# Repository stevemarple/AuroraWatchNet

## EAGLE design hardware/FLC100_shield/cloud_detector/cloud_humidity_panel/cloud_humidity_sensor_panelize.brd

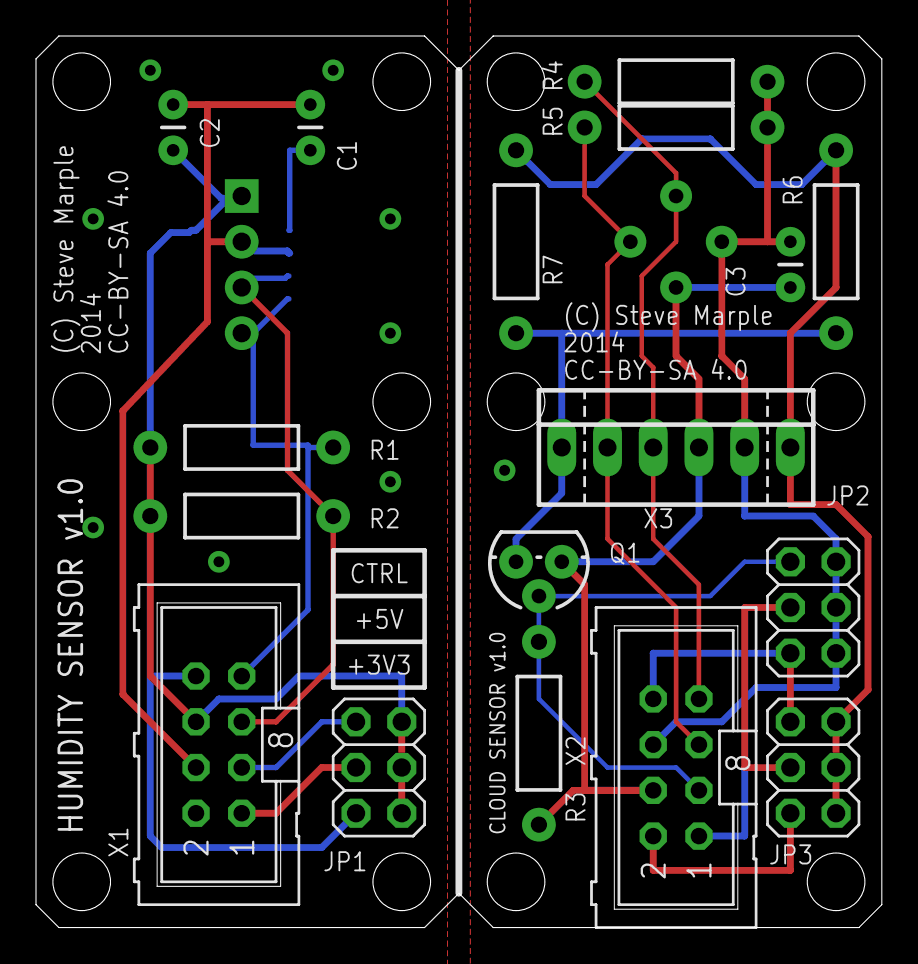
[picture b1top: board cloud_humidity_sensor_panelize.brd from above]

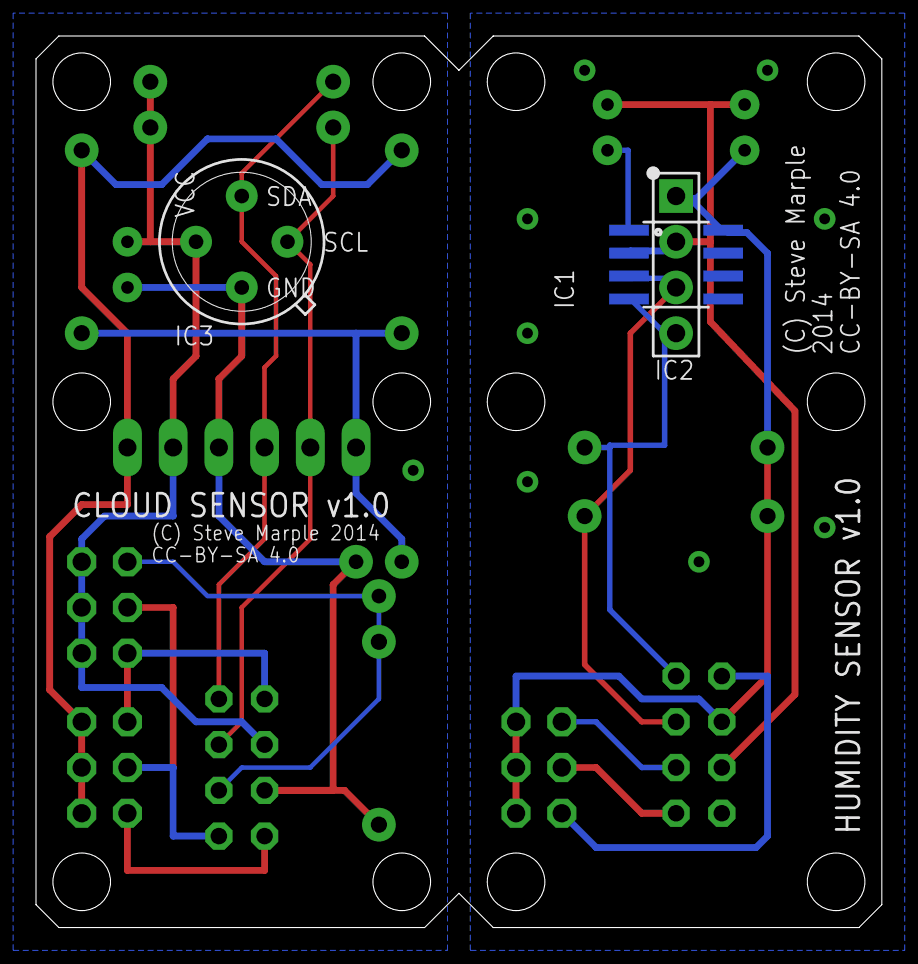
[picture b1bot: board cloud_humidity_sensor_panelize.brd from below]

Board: 2 copper layers, 47.0 x 49.5 mm, 20 parts (3 on the bottom side), 18 nets.

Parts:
C1, C3: 100n; CAP-PTH-SMALL
C2: 220n; CAP-PTH-SMALL
IC1: HIH613x; SO08
IC2: HIH612x; SIL04
IC3: MLX90614; TO39-4
JP1, JP2: VCC; 2X03
JP3: HEAT VCC; 2X03
Q1: 2N7000; TO-92
R1, R2, R4, R5: 10k; RES-AXIAL-0.4
R3: 1M; RES-AXIAL-0.4
R6, R7: 100R; RES-AXIAL-0.4
X1: FLC100 SHIELD; ML8
X2: SHIELD; ML8
X3: SENSOR; 22-23-2061

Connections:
+3V1: JP2.2, JP3.1, X2.8
+3V3: JP1.2, X1.8
+5V: JP1.4, X1.1
+5V1: JP2.4, JP3.3, X2.1
CONTROL: JP1.6, X1.3
CONTROL1: JP2.6, Q1.2, R3.P$2, X2.3
GND: C1.2, C2.2, IC1.2, IC2.2, X1.4
GND1: C3.2, IC3.4, Q1.1, R3.P$1, X2.4, X3.4
HEATER_CONTROL: Q1.3, R6.P$1, R7.P$1, X3.1
HEATER_VCC: JP3.2, JP3.4, JP3.6, R6.P$2, R7.P$2, X3.6
unnamed: C1.1, IC1.1
SCL: IC1.3, IC2.3, R2.P$1, X1.5
SCL1: IC3.1, R5.P$1, X2.5, X3.2
SDA: IC1.4, IC2.4, R1.P$1, X1.7
SDA1: IC3.2, R4.P$1, X2.7, X3.3
VCC: C2.1, IC1.8, IC2.1, JP1.1, JP1.3, JP1.5, R1.P$2, R2.P$2, X1.6
VCC1: C3.1, IC3.3, JP2.1, JP2.3, JP2.5, R4.P$2, R5.P$2, X2.6, X3.5
VIN1: JP3.5, X2.2

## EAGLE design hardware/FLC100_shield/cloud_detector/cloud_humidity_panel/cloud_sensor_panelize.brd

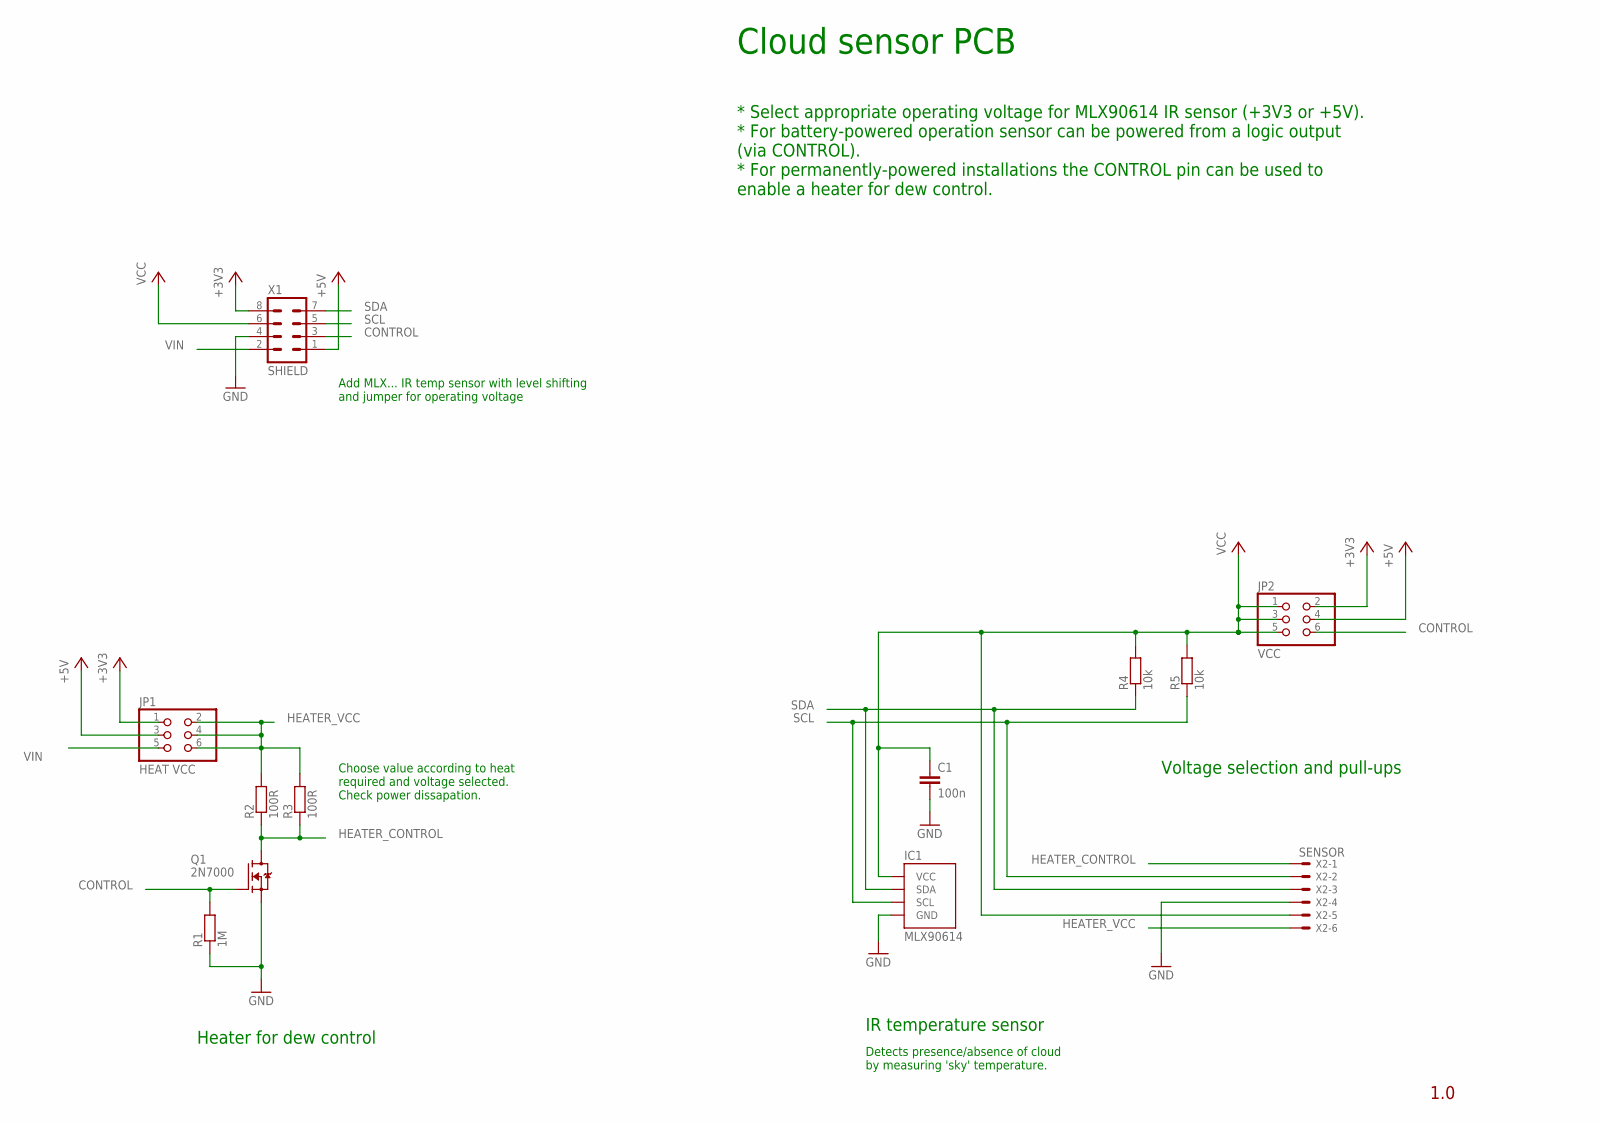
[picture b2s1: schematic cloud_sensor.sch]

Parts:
C1: 100n; CAP-PTH-SMALL
IC1: MLX90614; TO39-4
JP1: HEAT VCC; 2X03
JP2: VCC; 2X03
Q1: 2N7000; TO-92
R1: 1M; RES-AXIAL-0.4
R2, R3: 100R; RES-AXIAL-0.4
R4, R5: 10k; RES-AXIAL-0.4
X1: SHIELD; ML8
X2: SENSOR; 22-23-2061

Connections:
+3V3: JP1.1, JP2.2, X1.8
+5V: JP1.3, JP2.4, X1.1
CONTROL: JP2.6, Q1.2 (G), R1.P$2 (2), X1.3
GND: C1.2, IC1.4 (GND), Q1.1 (S), R1.P$1 (1), X1.4, X2.4
HEATER_CONTROL: Q1.3 (D), R2.P$1 (1), R3.P$1 (1), X2.1
HEATER_VCC: JP1.2, JP1.4, JP1.6, R2.P$2 (2), R3.P$2 (2), X2.6
SCL: IC1.1 (SCL), R5.P$1 (1), X1.5, X2.2
SDA: IC1.2 (SDA), R4.P$1 (1), X1.7, X2.3
VCC: C1.1, IC1.3 (VCC), JP2.1, JP2.3, JP2.5, R4.P$2 (2), R5.P$2 (2), X1.6, X2.5
VIN: JP1.5, X1.2

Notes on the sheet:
Add MLX... IR temp sensor with level shifting and jumper for operating voltage
Choose value according to heat required and voltage selected. Check power dissapation.
IR temperature sensor
Detects presence/absence of cloud by measuring 'sky' temperature.
Cloud sensor PCB
* Select appropriate operating voltage for MLX90614 IR sensor (+3V3 or +5V). * For battery-powered operation sensor can be powered from a logic output (via CONTROL). * For permanently-powered installations the CONTROL pin can be used to enable a heater for dew control.
Voltage selection and pull-ups
Heater for dew control
1.0

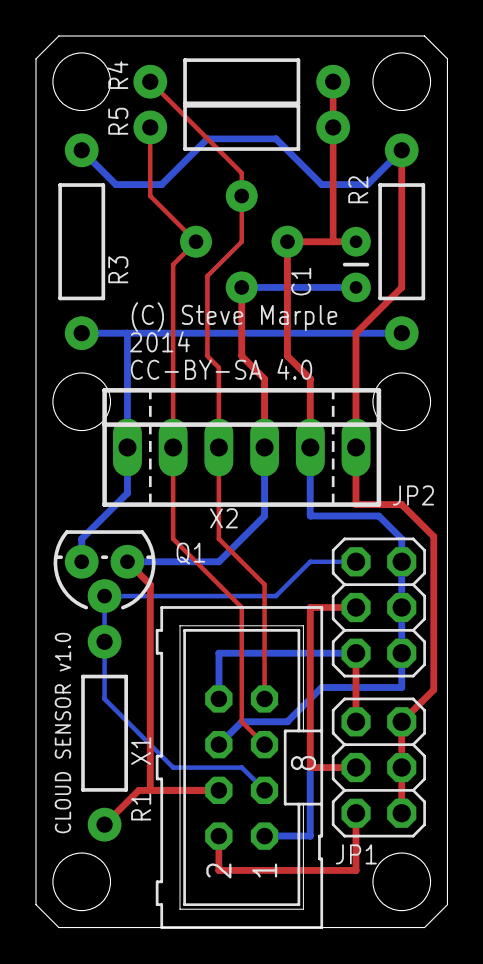
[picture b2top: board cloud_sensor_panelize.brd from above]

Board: 2 copper layers, 22.9 x 49.5 mm, 12 parts (1 on the bottom side), 10 nets.

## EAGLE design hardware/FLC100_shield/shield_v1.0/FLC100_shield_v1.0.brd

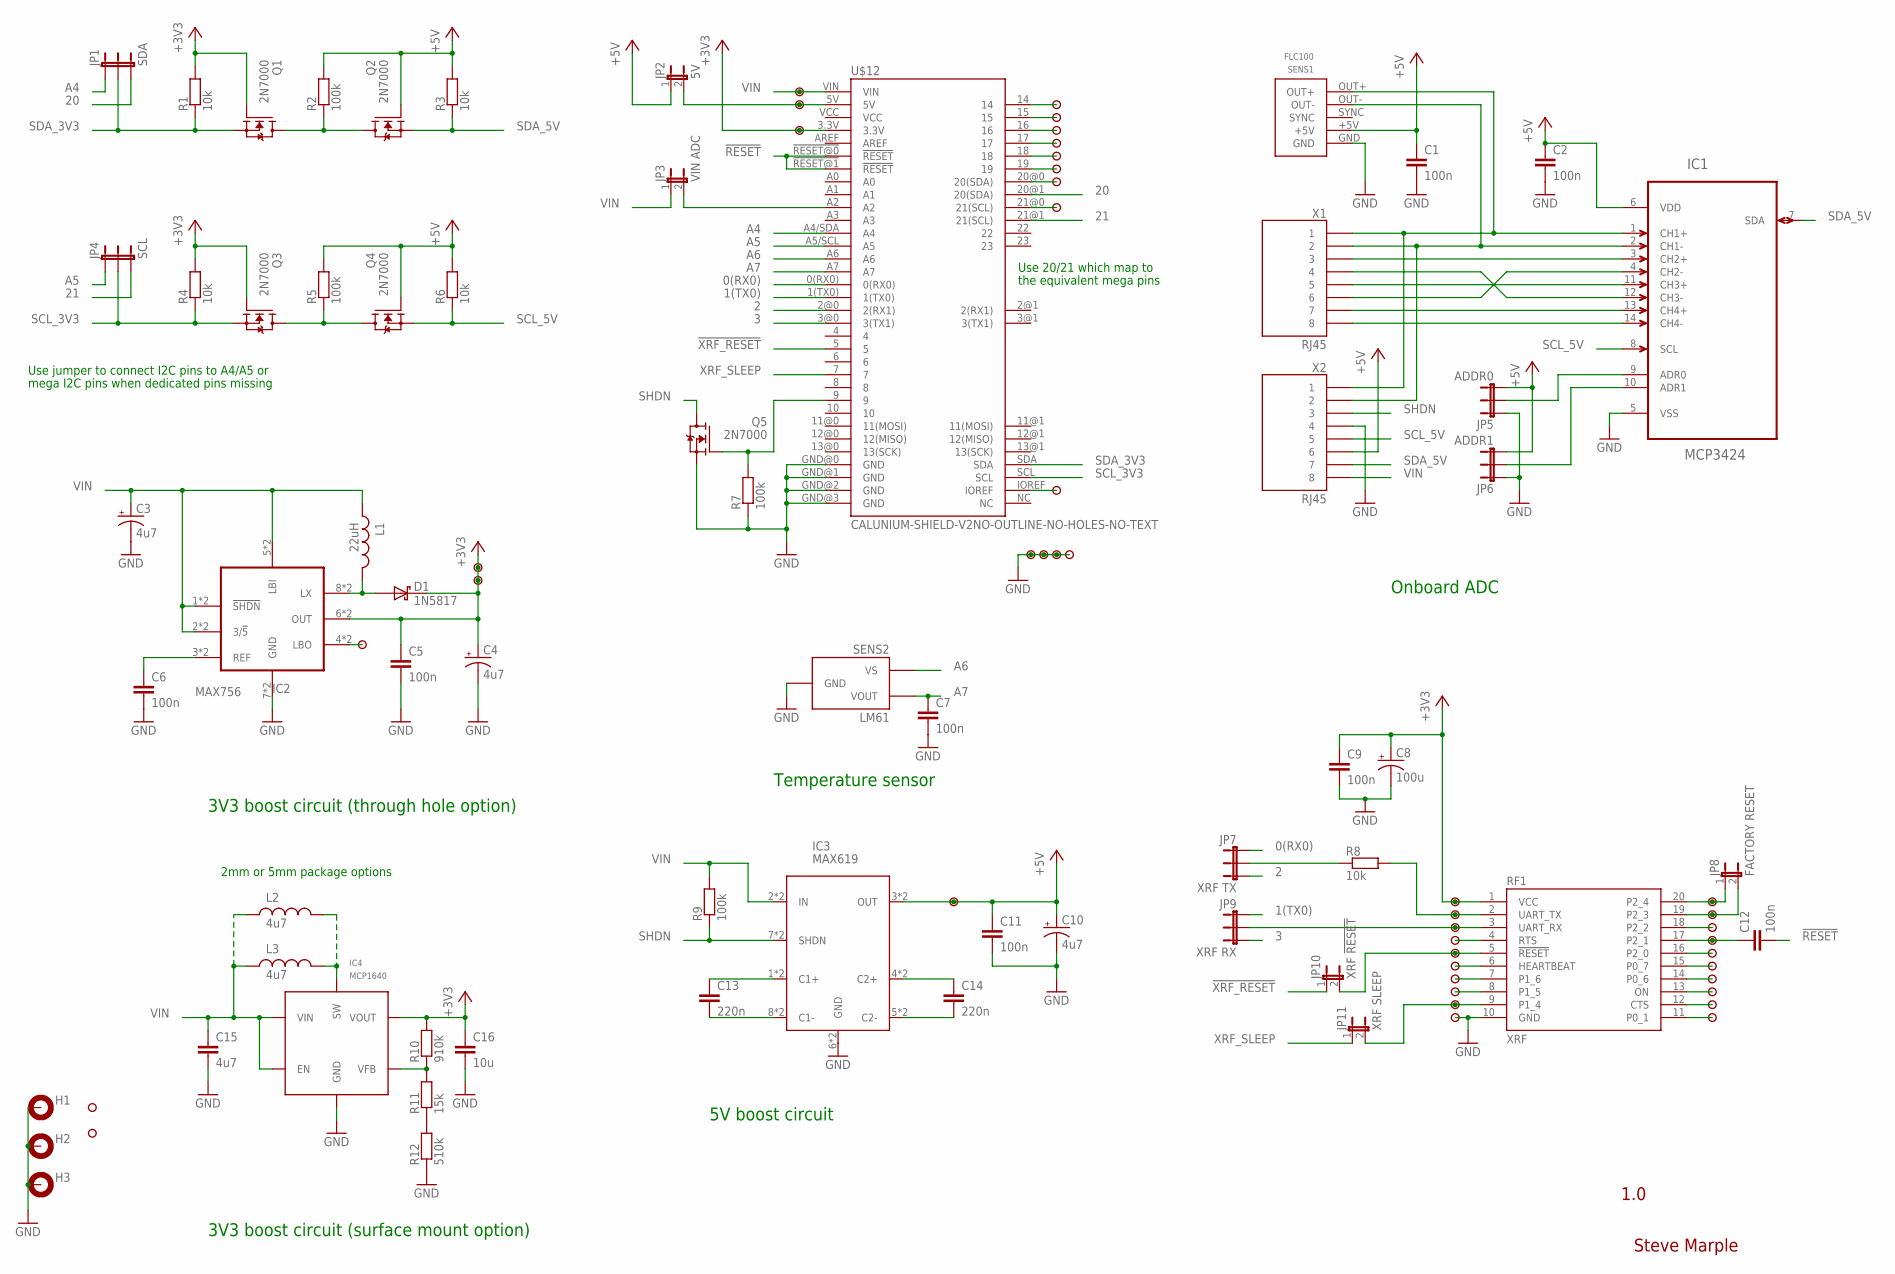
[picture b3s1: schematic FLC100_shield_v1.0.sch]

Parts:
C1, C2, C5, C6, C7, C9, C11, C12: 100n; CAP-PTH-SMALL
C3, C4, C10: 4u7; CPOL-RADIAL-10UF-25V
C8: 100u; CPOL-RADIAL-10UF-25V
C13, C14: 220n; CAP-PTH-5MM
C15: 4u7; 1206-HAND
C16: 10u; 1206-HAND
D1: 1N5817; DIODE-TH-0.4
H1, H2, H3: MOUNT-PAD-ROUND3.0; 3,0-PAD
IC1: MCP3424; SOIC127P600X175-14N
IC2: MAX756; DIL08-SOIC8
IC3: MAX619; DIL08-SOIC8
IC4: MCP1640; SOT23-6
JP1: SDA; 1X03
JP2: 5V; 1X02
JP3: VIN ADC; 1X02
JP4: SCL; 1X03
JP5: ADDR0; 1X03
JP6: ADDR1; 1X03
JP7: XRF TX; 1X03
JP8: FACTORY RESET; 1X02
JP9: XRF RX; 1X03
JP10: XRF !RESET; 1X02
JP11: XRF SLEEP; 1X02
L1: 22uH; INDUCTOR-TH-5MM
L2: 4u7; INDUCTOR-TH-2MM
L3: 4u7; INDUCTOR-TH-5MM
Q1, Q2, Q3, Q4, Q5: 2N7000; TO-92
R1, R3, R4, R6, R8: 10k; RES-AXIAL-0.4
R2, R5, R7, R9: 100k; RES-AXIAL-0.4
R10: 910k; 1206-HAND
R11: 15k; 1206-HAND
R12: 510k; 1206-HAND
RF1: XRF; XBEE
SENS1: FLC100
SENS2: LM61; TO-92
U$1, U$2, U$3, U$4, U$5, U$6, U$7, U$8, U$9, U$10, U$11, U$13, U$14, U$15, U$16, U$17, U$18, U$19, U$20, U$21, U$22, U$23, U$24, U$25, U$26, U$27, U$28, U$29, U$30, U$31, U$32, U$33, U$34, U$35, U$36, U$37, U$38, U$39, U$40, U$41, U$42, U$43: PAD
U$12: CALUNIUM-SHIELD-V2NO-OUTLINE-NO-HOLES-NO-TEXT; CALUNIUM-SHIELD-NO-OUTLINE-NO-HOLES-NO-TEXT-V2
X1, X2: RJ45; RJ45-8

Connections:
0(RX0): JP7.1, U$12.0(RX0)
1(TX0): JP9.1, U$12.1(TX0)
2: JP7.3, U$12.2@0 (2(RX1))
3: JP9.3, U$12.3@0 (3(TX1))
20: JP1.3, U$12.20@1 (20(SDA))
21: JP4.3, U$12.21@1 (21(SCL))
!RESET: C12.2, U$12.!RESET@0 (!RESET), U$12.!RESET@1 (!RESET)
!XRF_RESET: JP10.1, U$12.5
+3V3: C4.1 (+), C5.1, C8.1 (+), C9.1, C16.1, D1.C, IC2.6 (OUT), IC2.6@1 (OUT), IC4.5 (VOUT), Q1.2 (G), Q3.2 (G), R1.P$2 (2), R4.P$2 (2), R10.2, RF1.1 (VCC), U$5.1, U$12.3.3V, U$18.1, U$19.1, U$22.1
+5V: C1.1, C2.1, C10.1 (+), C11.1, IC1.6 (VDD), IC3.3 (OUT), IC3.3@1 (OUT), JP2.1, JP5.3, JP6.3, Q2.2 (G), Q4.2 (G), R2.P$2 (2), R3.P$2 (2), R5.P$2 (2), R6.P$2 (2), SENS1.+5V, U$21.1, X2.6
A4: JP1.1, U$12.A4/SDA (A4)
A5: JP4.1, U$12.A5/SCL (A5)
A6: SENS2.1 (VS), U$12.A6
A7: C7.1, SENS2.2 (VOUT), U$12.A7
CHECK1: IC1.9 (ADR0), JP5.2
CHECK2: IC1.10 (ADR1), JP6.2
GND: C1.2, C2.2, C3.2 (-), C4.2 (-), C5.2, C6.2, C7.2, C8.2 (-), C9.2, C10.2 (-), C11.2, C15.2, C16.2, H1.B3,0, H2.B3,0, H3.B3,0, IC1.5 (VSS), IC2.7 (GND), IC2.7@1 (GND), IC3.6 (GND), IC3.6@1 (GND), IC4.2 (GND), JP5.1, JP6.1, Q5.1 (S), R7.P$1 (1), R12.1, RF1.10 (GND), SENS1.GND, SENS2.3 (GND), U$12.GND@0 (GND), U$12.GND@1 (GND), U$12.GND@2 (GND), U$12.GND@3 (GND), U$14.1, U$15.1, U$16.1, U$17.1, U$40.1, X2.4
unnamed: Q1.3 (D), Q2.3 (D), R2.P$1 (1)
unnamed: Q3.3 (D), Q4.3 (D), R5.P$1 (1)
unnamed: C13.2, IC3.8 (C1-), IC3.8@1 (C1-)
unnamed: C13.1, IC3.1 (C1+), IC3.1@1 (C1+)
unnamed: C14.1, IC3.4 (C2+), IC3.4@1 (C2+)
unnamed: C14.2, IC3.5 (C2-), IC3.5@1 (C2-)
unnamed: JP8.1, RF1.20 (P2_4), U$23.1
unnamed: JP8.2, RF1.19 (P2_3), U$25.1
unnamed: R8.P$2 (2), RF1.2 (UART_TX), U$24.1
unnamed: JP9.2, RF1.3 (UART_RX), U$26.1
unnamed: RF1.4 (RTS), U$28.1
unnamed: JP10.2, RF1.5 (!RESET), U$30.1
unnamed: RF1.6 (HEARTBEAT), U$32.1
unnamed: RF1.7 (P1_6), U$34.1
unnamed: RF1.8 (P1_5), U$36.1
unnamed: JP11.2, RF1.9 (P1_4), U$38.1
unnamed: RF1.18 (P2_2), U$27.1
unnamed: C12.1, RF1.17 (P2_1), U$29.1
unnamed: RF1.16 (P2_0), U$31.1
unnamed: RF1.15 (P0_7), U$33.1
unnamed: RF1.14 (P0_6), U$35.1
unnamed: RF1.13 (ON), U$37.1
unnamed: RF1.12 (CTS), U$39.1
unnamed: RF1.11 (P0_1), U$41.1
unnamed: IC2.4 (LBO), IC2.4@1 (LBO), U$20.1
unnamed: Q5.2 (G), R7.P$2 (2), U$12.9
unnamed: JP3.2, U$12.A2
unnamed: JP7.2, R8.P$1 (1)
unnamed: JP2.2, U$2.1, U$12.5V
unnamed: D1.A, IC2.8 (LX), IC2.8@1 (LX), L1.P$2 (2)
unnamed: C6.1, IC2.3 (REF), IC2.3@1 (REF)
unnamed: IC1.1 (CH1+), SENS1.OUT+, X1.1, X2.1
unnamed: IC1.2 (CH1-), SENS1.OUT-, X1.2, X2.2
unnamed: IC1.3 (CH2+), X1.3
unnamed: IC1.4 (CH2-), X1.6
unnamed: IC1.11 (CH3+), X1.5
unnamed: IC1.12 (CH3-), X1.4
unnamed: IC1.13 (CH4+), X1.7
unnamed: IC1.14 (CH4-), X1.8
unnamed: U$11.1, U$12.21@0 (21(SCL))
unnamed: IC4.1 (SW), L2.P$2 (2), L3.P$2 (2)
unnamed: R11.1, R12.2
unnamed: U$3.1, U$12.14
unnamed: U$4.1, U$12.15
unnamed: U$6.1, U$12.16
unnamed: IC4.4 (VFB), R10.1, R11.2
unnamed: U$7.1, U$12.17
unnamed: U$8.1, U$12.18
unnamed: U$9.1, U$12.19
unnamed: U$10.1, U$12.20@0 (20(SDA))
unnamed: U$12.IOREF, U$13.1
SCL_3V3: JP4.2, Q3.1 (S), R4.P$1 (1), U$12.SCL
SCL_5V: IC1.8 (SCL), Q4.1 (S), R6.P$1 (1), X2.5
SDA_3V3: JP1.2, Q1.1 (S), R1.P$1 (1), U$12.SDA
SDA_5V: IC1.7 (SDA), Q2.1 (S), R3.P$1 (1), X2.7
SHDN: IC3.7 (SHDN), IC3.7@1 (SHDN), Q5.3 (D), R9.P$1 (1), X2.3
VIN: C3.1 (+), C15.1, IC2.1 (!SHDN), IC2.1@1 (!SHDN), IC2.2 (3/!5), IC2.2@1 (3/!5), IC2.5 (LBI), IC2.5@1 (LBI), IC3.2 (IN), IC3.2@1 (IN), IC4.3 (EN), IC4.6 (VIN), JP3.1, L1.P$1 (1), L2.P$1 (1), L3.P$1 (1), R9.P$2 (2), U$1.1, U$12.VIN, X2.8
XRF_SLEEP: JP11.1, U$12.7

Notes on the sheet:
1.0
Steve Marple
Use jumper to connect I2C pins to A4/A5 or
3V3 boost circuit (through hole option)
Use 20/21 which map to
the equivalent mega pins
2mm or 5mm package options
mega I2C pins when dedicated pins missing
3V3 boost circuit (surface mount option)
Onboard ADC
5V boost circuit
Temperature sensor

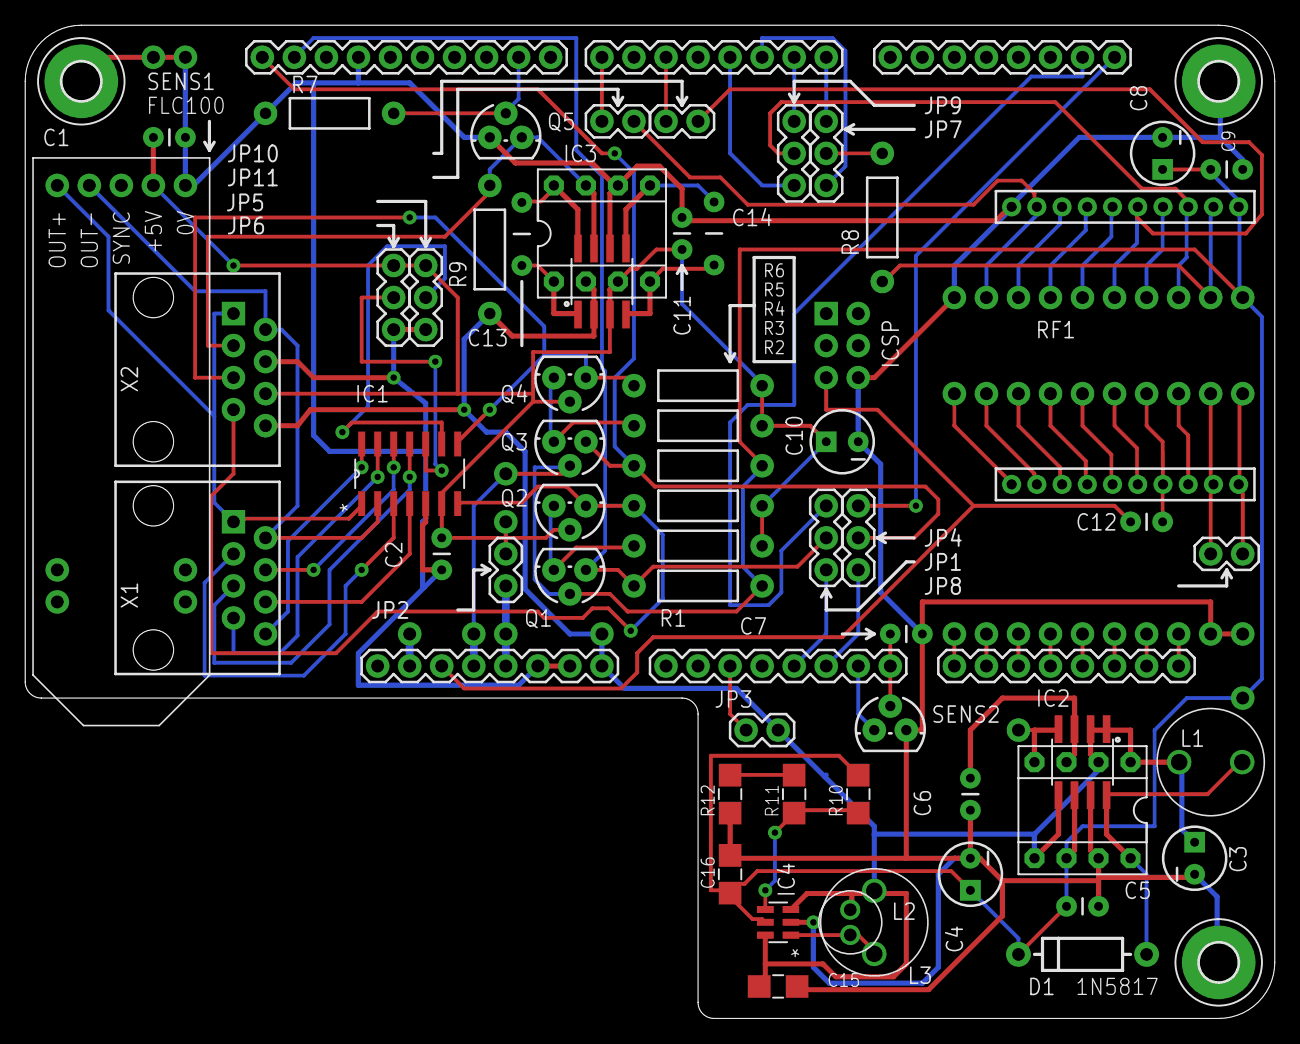
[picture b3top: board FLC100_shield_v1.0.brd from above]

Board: 2 copper layers, 99.1 x 78.7 mm, 103 parts (0 on the bottom side), 75 nets.

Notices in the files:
hardware/FLC100_shield/cloud_detector/cloud_humidity_panel/cloud_humidity_sensor_panelize.brd:
CC-BY-SA 4.0
parts and their libraries:
SparkFun: Licensing: CC v3.0 Share-Alike You are welcome to use this library for commercial purposes.
